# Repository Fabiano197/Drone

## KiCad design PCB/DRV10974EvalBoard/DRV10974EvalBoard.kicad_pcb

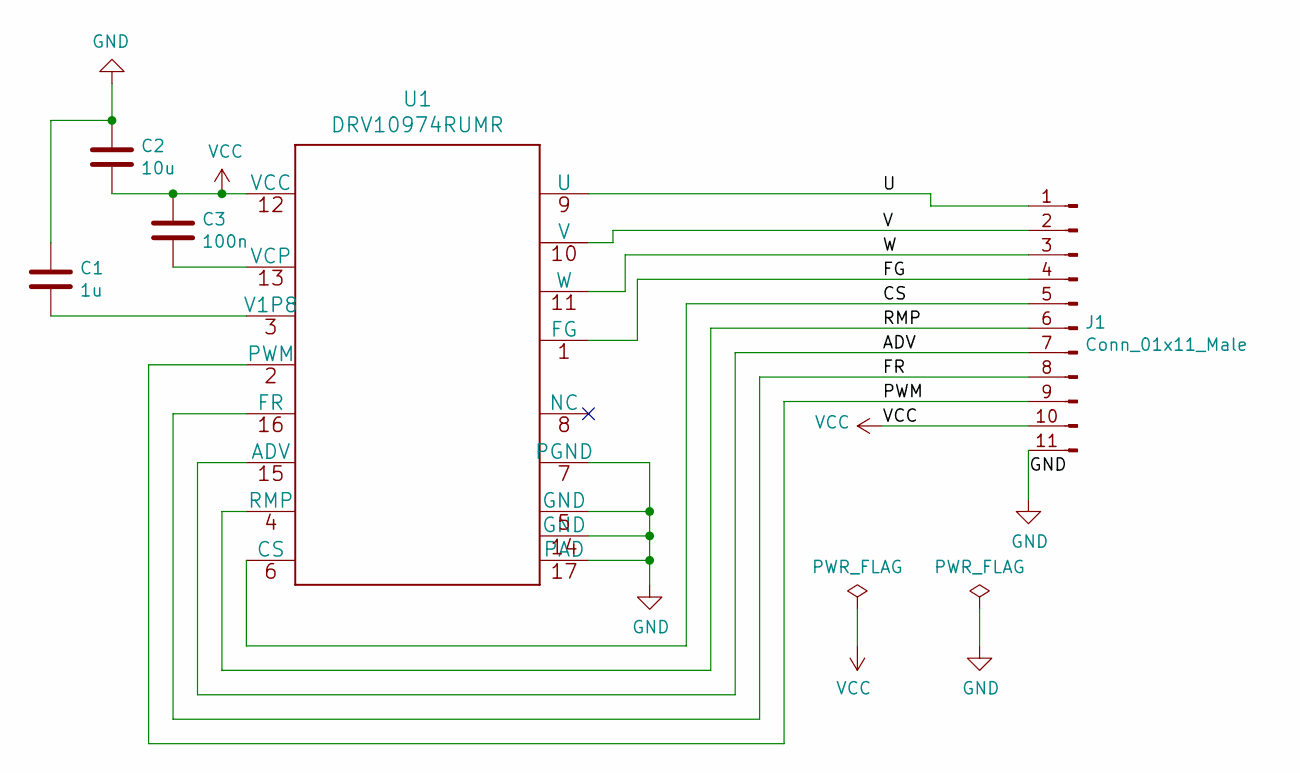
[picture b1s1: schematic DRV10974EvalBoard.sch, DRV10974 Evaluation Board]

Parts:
C1: 1u; C_1206_3216Metric_Pad1.33x1.80mm_HandSolder
C2: 10u; C_1206_3216Metric_Pad1.33x1.80mm_HandSolder
C3: 100n; C_1206_3216Metric_Pad1.33x1.80mm_HandSolder
J1: Conn_01x11_Male; PinHeader_1x11_P2.54mm_Vertical
U1: DRV10974RUMR

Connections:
/ADV: J1.7, U1.15 (ADV)
/CS: J1.5, U1.6 (CS)
/FG: J1.4, U1.1 (FG)
/FR: J1.8, U1.16 (FR)
/PWM: J1.9, U1.2 (PWM)
/RMP: J1.6, U1.4 (RMP)
/U: J1.1, U1.9 (U)
/V: J1.2, U1.10 (V)
/W: J1.3, U1.11 (W)
GND: C1.1, C2.1, J1.11, U1.5 (GND), U1.7 (PGND), U1.14 (GND), U1.17 (PAD), U1.V
unnamed: C1.2, U1.3 (V1P8)
unnamed: C3.2, U1.13 (VCP)
VCC: C2.2, C3.1, J1.10, U1.12 (VCC)

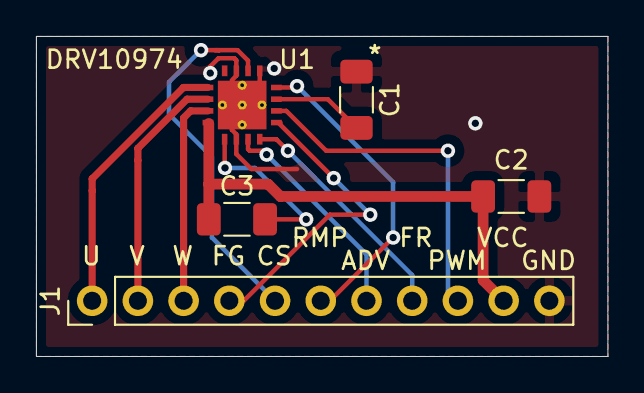
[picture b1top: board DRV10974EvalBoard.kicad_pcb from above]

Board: 2 copper layers, 31.8 x 17.8 mm, 5 parts (0 on the bottom side), 13 nets.

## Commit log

2021-08-20 Drivers
    Driver for motor, battery state and TOF sensor
2021-08-23 Motor Testing
    Test Data of Mabuchi RD-180SA-3532
2021-08-26 Add DRV10974 Eval Board schematic and design

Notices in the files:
parts and their libraries:
Copyright 2021 Accelerated Designs. All rights reserved.
